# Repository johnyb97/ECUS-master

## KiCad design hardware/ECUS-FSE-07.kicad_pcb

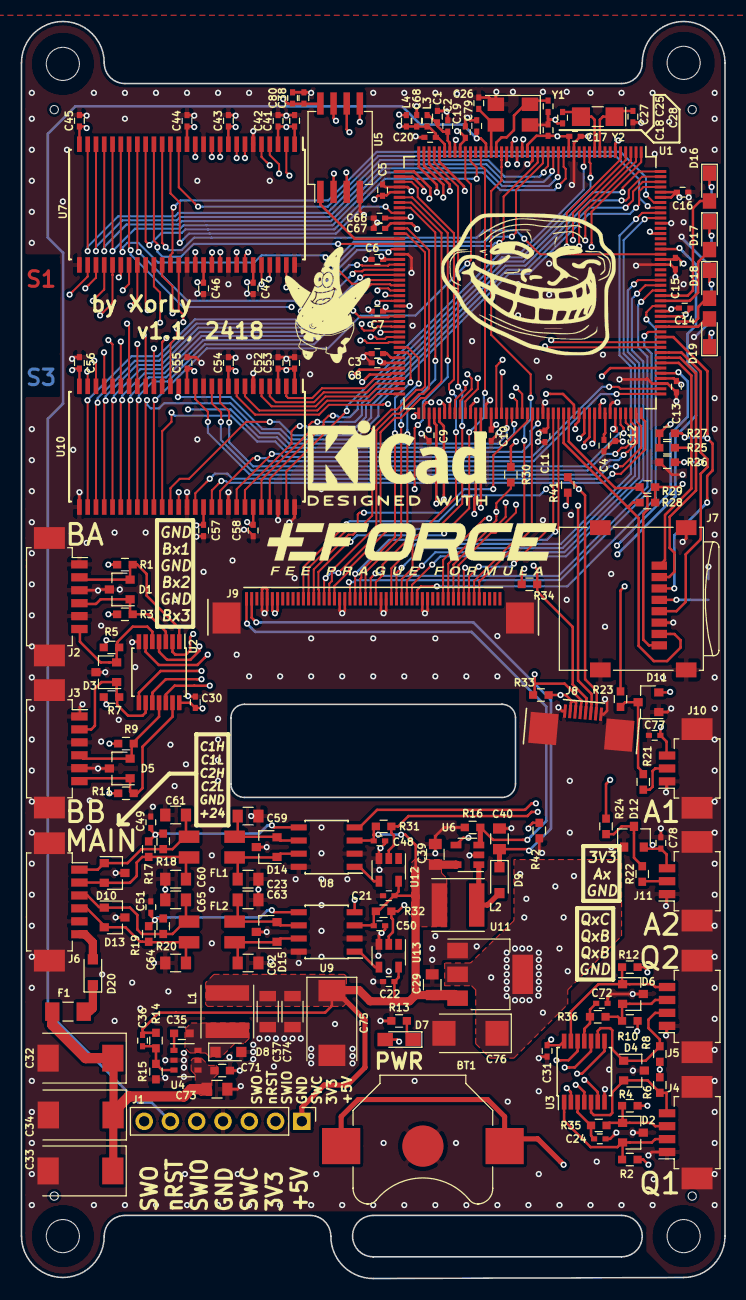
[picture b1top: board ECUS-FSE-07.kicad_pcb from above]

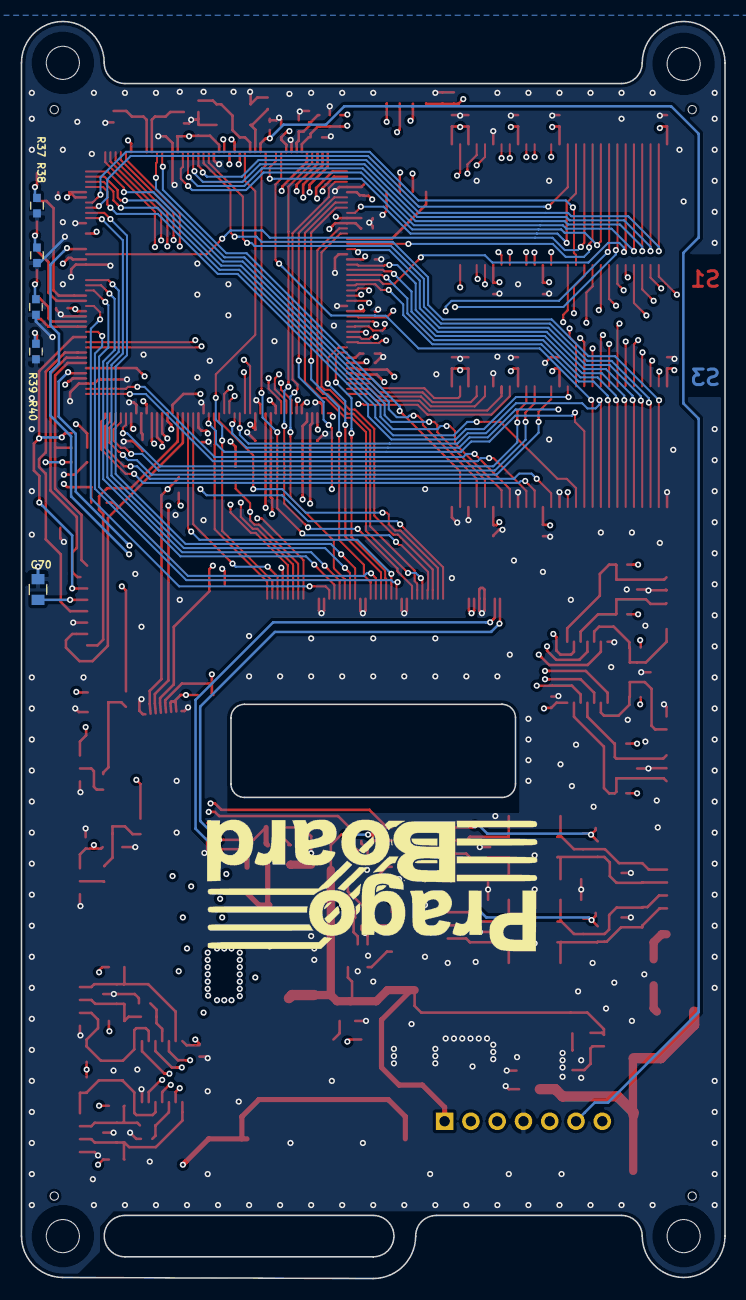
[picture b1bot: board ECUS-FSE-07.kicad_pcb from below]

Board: 6 copper layers, 68.0 x 121.5 mm, 189 parts (6 on the bottom side), 184 nets.

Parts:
BT1: BR-1225/VCN; Keystone_3000_1x12mm-CoinCell
C1, C3, C4, C68: 2.2u; C_0402_1005Metric_legacy
C2, C5, C6, C7, C8, C9, C10, C11, C12, C13, C14, C15, C16, C17, C18, C19, C20, C21, C22, C24, C30, C31, C36, C38, C48, C50, C72, C79: 100n; C_0402_1005Metric_legacy
C23, C59, C60, C61, C62, C63, C64, C65: Can; C_0805_2012Metric_legacy
C25, C26: 33p; C_0402_1005Metric_legacy
C27, C28: 15p; C_0402_1005Metric_legacy
C29, C39: 4.7u; C_0805_2012Metric_legacy
C32, C33, C34: 10u/35V; CP_EIA-7343-31_Kemet-D
C35: 15n/50V; C_0603_1608Metric_legacy
C37, C74: 10u; C_1206_3216Metric_legacy
C40: 220n/35V; C_0805_2012Metric_legacy
C41, C42, C43, C44, C45, C46, C47, C49, C51, C52, C53, C54, C55, C56, C57, C58: 10n; C_0402_1005Metric_legacy
C66, C67: Cain; C_0402_1005Metric_legacy
C70: 4u; C_0805_2012Metric_legacy
C71: 100n/50V; C_0603_1608Metric_legacy
C73: 1u/50V; C_0805_2012Metric_legacy
C75: 100u/10V; CP_EIA-7343-31_Kemet-D
C76: 22u/16V; CP_EIA-6032-28_Kemet-C_Pad2.24x2.40mm_HandSolder
C77, C78: C; C_0402_1005Metric_legacy
C80: 1u; C_0402_1005Metric_legacy
D1, D2, D3, D4, D5, D6: D_TVS_UNI_x2_CCA; SOT-23
D7: PWR; LED_0805_2012Metric_Pad0.97x1.50mm_HandSolder
D8, D9, D20: D_Schottky; D_SOD-323_HandSoldering
D10, D13, D14, D15: NUP2105L; SOT-23
D11, D12: BAV99; SOT-23
D16: LED1; LED_0805_2012Metric_Pad0.97x1.50mm_HandSolder
D17: LED2; LED_0805_2012Metric_Pad0.97x1.50mm_HandSolder
D18: LED3; LED_0805_2012Metric_Pad0.97x1.50mm_HandSolder
D19: LED4; LED_0805_2012Metric_Pad0.97x1.50mm_HandSolder
F1: Fuse; Fuse_1206_3216Metric_Pad1.39x1.80mm_HandSolder
FL1, FL2: EMI_Filter_LL; DLW43
J1: DBG; PinHeader_1x07_P2.54mm_Vertical
J2: BTN_A; Molex_PicoBlade_53261-0671_1x06-1MP_P1.25mm_Horizontal
J3: BTN_B; Molex_PicoBlade_53261-0671_1x06-1MP_P1.25mm_Horizontal
J4: QEI1; Molex_PicoBlade_53261-0471_1x04-1MP_P1.25mm_Horizontal
J5: QEI2; Molex_PicoBlade_53261-0471_1x04-1MP_P1.25mm_Horizontal
J6: main; Molex_PicoBlade_53261-0671_1x06-1MP_P1.25mm_Horizontal
J7: Micro_SD_Card_Det; microSD_HC_Wuerth_693072010801
J8: TC; FPC_08_0.5
J9: LCD; FPC_50_0.5
J10, J11: AIN; Molex_PicoBlade_53261-0371_1x03-1MP_P1.25mm_Horizontal
L1: 6.8u; L_Taiyo-Yuden_NR-50xx
L2: 33u; L_Taiyo-Yuden_NR-50xx
L3, L4: Ferrite_Bead_Small; C_0402_1005Metric_legacy
M1: DISPLAY_MODEL; LCD_ECUS
M2: eforce; eforce_28
M3: pragoboard
M4: bonus; troll_24
M5: kicad; kicad_18
M6: patrick; patrick_11
MK1, MK2, MK3, MK4: Mounting_Hole; MountingHole_3.2mm_M3_NoMask
MK5, MK6, MK7, MK8: LCD_Hole; Hole_0.8
R1, R2, R3, R4, R5, R6, R7, R8, R9, R10, R11, R12, R31, R32, R35, R36, R42: 1k; R_0603_larger_pads
R13, R37, R38, R39, R40: Rled; R_0603_larger_pads
R14: 3.9k; R_0603_larger_pads
R15: 680; R_0603_larger_pads
R16: 15; R_0603_larger_pads
R17, R18, R19, R20: 60; R_0603_larger_pads
R21, R22: Rain; R_0603_larger_pads
R23, R24: Rain2; R_0603_larger_pads
R25, R27, R28, R29: RuSD; R_0603_larger_pads
R26: RdSD; R_0603_larger_pads
R30, R41: 10k; R_0603_larger_pads
R33, R34: 4.7k; R_0603_larger_pads
U1: STM32F746IETx; LQFP-176_24x24mm_P0.5mm
U2, U3: 74LVC04; TSSOP-14_4.4x5mm_P0.65mm
U4: BD9G101G; TSOP-6_1.65x3.05mm_P0.95mm
U5: N25Q128A; SSO-8_6.8x5.9mm_P1.27mm_Clearance7mm
U6: CAT4237; SOT-23-5
U7, U10: IS42S16400; TSOP_II_54_10.16x22.22_Pitch0.8mm
U8, U9: TJA1049T; SOIC-8_3.9x4.9mm_P1.27mm
U11: AP1117-33; SOT-223-3_TabPin2
U12, U13: 74LVC1G17; SOT-23-5
Y1: 8MHz 18pF; Crystal_SMD_5032-4Pin_5.0x3.2mm
Y2: 32.768 kHz 9pF; Crystal_SMD_MicroCrystal_CC7V-T1A-2Pin_3.2x1.5mm_HandSolder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

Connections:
+3V3: C5.1, C6.1, C7.1, C8.1, C9.1, C10.1, C11.1, C12.1, C13.1, C14.1, C15.1, C16.1, C17.1, C18.1, C19.1, C30.1, C31.1, C38.1, C41.1, C42.1, C43.1, C44.1, C45.1, C46.1, C47.1, C52.1, C53.1, C54.1, C55.1, C56.1, C57.1, C58.1, C70.1, C76.1, C77.2, C78.2, C80.1, D7.2, D11.2, D12.2, J1.2, J7.4, J8.2, J8.3, J9.6, J9.7, J10.3, J11.3, L4.2, R1.1, R2.1, R3.1, R4.1, R5.1, R6.1, R7.1, R8.1, R9.1, R10.1, R11.1, R12.1, R25.1, R27.1, R28.1, R29.1, R30.1, R33.1, R34.1, R41.1, U1.15, U1.23, U1.36, U1.49, U1.62, U1.72, U1.82, U1.91, U1.103, U1.114, U1.127, U1.136, U1.149, U1.159, U1.171, U1.172, U2.14, U3.14, U5.8, U7.1, U7.3, U7.9, U7.14, U7.27, U7.43, U7.49, U10.1, U10.3, U10.9, U10.14, U10.27, U10.43, U10.49, U11.2
+5V: C21.1, C22.1, C29.1, C36.1, C37.1, C39.1, C48.1, C50.1, C74.1, C75.1, J1.1, L1.2, L2.1, R14.1, R31.1, R32.1, U6.5, U8.3, U9.3, U11.3, U12.5, U13.5
+24V: C32.1, C33.1, C34.1, C71.1, C73.1, F1.2, U4.4, U4.5
/AIN_1: C66.2, R23.2, U1.54
/AIN_2: C67.2, R24.2, U1.55
/BTN_A1: U1.83, U2.2
/BTN_A2: U1.84, U2.4
/BTN_A3: U1.94, U2.6
/BTN_B1: U1.95, U2.8
/BTN_B2: U1.99, U2.10
/BTN_B3: U1.119, U2.12
/CAN1_H: C60.1, D10.2, FL1.2, J6.2, R17.1
/CAN1_L: C61.1, D10.1, FL1.4, J6.1, R18.2
/CAN1_RX: U1.122, U8.4
/CAN1_TX: R31.2, U1.123, U12.2
/CAN2_H: C64.1, D13.2, FL2.2, J6.4, R19.1
/CAN2_L: C65.1, D13.1, FL2.4, J6.3, R20.2
/CAN2_RX: U1.92, U9.4
/CAN2_TX: R32.2, U1.93, U13.2
/FLASH_CLK: U1.58, U5.1
/FLASH_IO0: U1.26, U5.5
/FLASH_IO1: U1.27, U5.2
/FLASH_IO2: U1.25, U5.3
/FLASH_IO3: U1.24, U5.7
/FLASH_nCS: U1.164, U5.6
/I2C4_SCL: J8.4, R33.2, U1.100
/I2C4_SDA: J8.5, R34.2, U1.101
/LCD/LED_A: C40.1, D9.1, J9.2
/LCD/LED_K: J9.1, R16.1, U6.3
/LCD_B2: J9.34, U1.150
/LCD_B3: J9.33, U1.154
/LCD_B4: J9.32, U1.155
/LCD_B5: J9.31, U1.47
/LCD_B6: J9.30, U1.167
/LCD_B7: J9.29, U1.168
/LCD_BLCTL: R42.1, U1.138, U6.4
/LCD_CLK: J9.46, U1.111
/LCD_CTL_MISO: J9.42, U1.4
/LCD_CTL_MOSI: J9.41, U1.5
/LCD_CTL_RST: J9.12, U1.2
/LCD_CTL_SCK: J9.39, U1.1
/LCD_CTL_~CS: J9.40, R30.2, U1.3
/LCD_DE: J9.45, U1.28
/LCD_G2: J9.26, U1.52
/LCD_G3: J9.25, U1.153
/LCD_G4: J9.24, U1.79
/LCD_G5: J9.23, U1.80
/LCD_G6: J9.22, U1.116
/LCD_G7: J9.21, U1.145
/LCD_HSYNC: J9.44, U1.115
/LCD_R2: J9.18, U1.41
/LCD_R3: J9.17, U1.56
/LCD_R4: J9.16, U1.51
/LCD_R5: J9.15, U1.32
/LCD_R6: J9.14, U1.57
/LCD_R7: J9.13, U1.110
/LCD_VSYNC: J9.43, U1.50
/LED1: D16.2, U1.152
/LED2: D17.2, U1.151
/LED3: D18.2, U1.147
/LED4: D19.2, U1.146
/QE1_A: U1.40, U3.2
/QE1_B: U1.42, U3.4
/QE1_C: U1.43, U3.6
/QE2_A: U1.44, U3.8
/QE2_B: U1.45, U3.10
/QE2_C: U1.46, U3.12
/RAM_A0: U1.16, U7.23, U10.23
/RAM_A1: U1.17, U7.24, U10.24
/RAM_A2: U1.18, U7.25, U10.25
/RAM_A3: U1.19, U7.26, U10.26
/RAM_A4: U1.20, U7.29, U10.29
/RAM_A5: U1.21, U7.30, U10.30
/RAM_A6: U1.60, U7.31, U10.31
/RAM_A7: U1.63, U7.32, U10.32
/RAM_A8: U1.64, U7.33, U10.33
/RAM_A9: U1.65, U7.34, U10.34
/RAM_A10: U1.66, U7.22, U10.22
/RAM_A11: U1.67, U7.35, U10.35
/RAM_A12: U1.106, U7.36, U10.36
/RAM_A13: U1.107, U7.40, U10.40
/RAM_BA0: U1.108, U7.20, U10.20
/RAM_BA1: U1.109, U7.21, U10.21
/RAM_CAS: U1.160, U7.17, U10.17
/RAM_CKE: U1.35, U7.37, U10.37
/RAM_CLK: U1.112, U7.38, U10.38
/RAM_CS: U1.34, U7.19, U10.19
/RAM_DE0: U1.169, U7.15
/RAM_DE1: U1.170, U7.39
/RAM_DE2: U1.173, U10.15
/RAM_DE3: U1.174, U10.39
/RAM_DH0: U1.85, U10.2
/RAM_DH1: U1.86, U10.4
/RAM_DH2: U1.87, U10.5
/RAM_DH3: U1.88, U10.7
/RAM_DH4: U1.89, U10.8
/RAM_DH5: U1.128, U10.10
/RAM_DH6: U1.129, U10.11
/RAM_DH7: U1.130, U10.13
/RAM_DH8: U1.131, U10.42
/RAM_DH9: U1.132, U10.44
/RAM_DH10: U1.133, U10.45
/RAM_DH11: U1.134, U10.47
/RAM_DH12: U1.175, U10.48
/RAM_DH13: U1.176, U10.50
/RAM_DH14: U1.11, U10.51
/RAM_DH15: U1.12, U10.53
/RAM_DL0: U1.104, U7.2
/RAM_DL1: U1.105, U7.4
/RAM_DL2: U1.142, U7.5
/RAM_DL3: U1.143, U7.7
/RAM_DL4: U1.68, U7.8
/RAM_DL5: U1.69, U7.10
/RAM_DL6: U1.70, U7.11
/RAM_DL7: U1.73, U7.13
/RAM_DL8: U1.74, U7.42
/RAM_DL9: U1.75, U7.44
/RAM_DL10: U1.76, U7.45
/RAM_DL11: U1.77, U7.47
/RAM_DL12: U1.78, U7.48
/RAM_DL13: U1.96, U7.50
/RAM_DL14: U1.97, U7.51
/RAM_DL15: U1.98, U7.53
/RAM_RAS: U1.59, U7.18, U10.18
/RAM_WE: U1.53, U7.16, U10.16
/SD_CLK: J7.5, U1.141
/SD_CMD: J7.3, R27.2, U1.144
/SD_DAT0: J7.7, R28.2, U1.117
/SD_DAT1: J7.8, R29.2, U1.118
/SD_DAT2: J7.1, R25.2, U1.139
/SD_DAT3: J7.2, R26.1, U1.140
/SWCLK: J1.3, U1.137
/SWDIO: J1.5, U1.124
/SWO: J1.7, U1.161
/TC_INT: J8.6, U1.120
/TC_RST: J8.7, R41.2, U1.121
/VDDA: C20.1, C68.1, L3.1, L4.1, U1.39
/XTAL32_IN: C27.1, U1.9, Y2.1
/XTAL32_OUT: C28.1, U1.10, Y2.2
/XTAL_IN: C25.1, U1.29, Y1.1
/XTAL_OUT: C26.1, U1.30, Y1.3
/nRST: C79.1, J1.6, U1.31
GND: BT1.2, C1.2, C2.2, C3.2, C4.2, C5.2, C6.2, C7.2, C8.2, C9.2, C10.2, C11.2, C12.2, C13.2, C14.2, C15.2, C16.2, C17.2, C18.2, C19.2, C20.2, C21.2, C22.2, C23.2, C24.2, C25.2, C26.2, C27.2, C28.2, C29.2, C30.2, C31.2, C32.2, C33.2, C34.2, C37.2, C38.2, C39.2, C40.2, C41.2, C42.2, C43.2, C44.2, C45.2, C46.2, C47.2, C48.2, C49.2, C50.2, C51.2, C52.2, C53.2, C54.2, C55.2, C56.2, C57.2, C58.2, C59.2, C60.2, C61.2, C62.2, C63.2, C64.2, C65.2, C66.1, C67.1, C68.2, C70.2, C71.2, C72.2, C73.2, C74.2, C75.2, C76.2, C77.1, C78.1, C79.2, C80.2, D1.3, D2.3, D3.3, D4.3, D5.3, D6.3, D8.2, D10.3, D11.1, D12.1, D13.3, D14.3, D15.3, J1.4, J2.1, J2.3, J2.5, J2.MP, J3.1, J3.3, J3.5, J3.MP, J4.1, J4.MP, J5.1, J5.MP, J6.5, J6.MP, J7.6, J7.9, J8.1, J8.8, J8.MP, J9.4, J9.5, J9.19, J9.20, J9.27, J9.28, J9.35, J9.36, J9.MP, J10.1, J10.MP, J11.1, J11.MP, R13.2, R15.2, R16.2, R26.2, R37.2, R38.2, R39.2, R40.2, R42.2, U1.14, U1.22, U1.37, U1.48, U1.61, U1.71, U1.90, U1.102, U1.113, U1.126, U1.135, U1.148, U1.158, U1.166, U2.7, U3.7, U4.2, U5.4, U6.2, U7.6, U7.12, U7.28, U7.41, U7.46, U7.52, U7.54, U8.2, U8.8, U9.2, U9.8, U10.6, U10.12, U10.28, U10.41, U10.46, U10.52, U10.54, U11.1, U12.3, U13.3, Y1.2, Y1.4
unnamed: BT1.1, U1.6
unnamed: C1.1, C2.1, L3.2, U1.38
unnamed: C3.1, U1.81
unnamed: C4.1, U1.125
unnamed: C23.1, D14.1, FL1.1, U8.7
unnamed: C24.1, R35.1, U3.3
unnamed: C35.1, D8.1, L1.1, U4.6
unnamed: C35.2, U4.1
unnamed: C36.2, R14.2, R15.1, U4.3
unnamed: C49.1, R17.2, R18.1, U8.5
unnamed: C51.1, R19.2, R20.1, U9.5
unnamed: C59.1, D14.2, FL1.3, U8.6
unnamed: C62.1, D15.1, FL2.1, U9.7
unnamed: C63.1, D15.2, FL2.3, U9.6
unnamed: C72.1, R36.1, U3.11
unnamed: D1.1, J2.4, R3.2, U2.3
unnamed: D1.2, J2.2, R1.2, U2.1
unnamed: D2.1, J4.3, R4.2, R35.2
unnamed: D2.2, J4.2, R2.2, U3.1
unnamed: D3.1, J3.2, R7.2, U2.9
unnamed: D3.2, J2.6, R5.2, U2.5
unnamed: D4.1, J5.2, R8.2, U3.9
unnamed: D4.2, J4.4, R6.2, U3.5
unnamed: D5.1, J3.6, R11.2, U2.13
unnamed: D5.2, J3.4, R9.2, U2.11
unnamed: D6.1, J5.4, R12.2, U3.13
unnamed: D6.2, J5.3, R10.2, R36.2
unnamed: D7.1, R13.1
unnamed: D9.2, L2.2, U6.1
unnamed: D11.3, R21.2, R23.1
unnamed: D12.3, R22.2, R24.1
unnamed: D16.1, R37.1
unnamed: D17.1, R38.1
unnamed: D18.1, R39.1
unnamed: D19.1, R40.1
unnamed: D20.1, F1.1
unnamed: D20.2, J6.6
unnamed: J10.2, R21.1
unnamed: J11.2, R22.1
unnamed: U8.1, U12.4
unnamed: U9.1, U13.4

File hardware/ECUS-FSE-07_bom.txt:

Reference, Quantity, Value, Footprint, Datasheet, mpn

mouser
BT1 ,1,"BR-1225/VCN","efoce_misc:Keystone_3000_1x12mm-CoinCell","","3000"
D10 D13 D14 D15 ,4,"NUP2105L","Package_TO_SOT_SMD:SOT-23","","SZNUP2105LT3G"
D11 D12 ,2,"BAV99","Package_TO_SOT_SMD:SOT-23","","BAV99"
D1 D2 D3 D4 D5 D6 ,6,"D_TVS_UNI_x2_CCA","Package_TO_SOT_SMD:SOT-23","","PESD3V3S2UT"
D8 D9 ,2,"D_Schottky","Diode_SMD:D_SOD-323_HandSoldering","","CMDSH05-45 TR"
F1 ,1,"Fuse","Fuse:Fuse_1206_3216Metric_Pad1.24x1.80mm_HandSolder","","C1Q 250"
FL1 FL2 ,2,"EMI_Filter_LL","eforce_misc:DLW43","","DLW43SH510XK2L"
J10 J11 ,2,"AIN","Connectors_Molex:Molex_PicoBlade_53261-0371_03x1.25mm_Angled","","53261-0371"
J2 ,1,"BTN_A","Connectors_Molex:Molex_PicoBlade_53261-0671_06x1.25mm_Angled","","53261-0671"
J3 ,1,"BTN_B","Connectors_Molex:Molex_PicoBlade_53261-0671_06x1.25mm_Angled","","53261-0671"
J4 ,1,"QE1","Connectors_Molex:Molex_PicoBlade_53261-0471_04x1.25mm_Angled","","53261-0471"
J5 ,1,"QE2","Connectors_Molex:Molex_PicoBlade_53261-0471_04x1.25mm_Angled","","53261-0471"
J6 ,1,"main","Connectors_Molex:Molex_PicoBlade_53261-0771_07x1.25mm_Angled","","53261-0771"
R16 ,1,"15","Capacitor_SMD_legacy:C_0603_1608Metric","","CRCW060315R0FKEA"
U2 U3 ,2,"74LVC04","Package_SO:TSSOP-14_4.4x5mm_P0.65mm","","SN74LVC04APWR"
U5 ,1,"N25Q128A","Package_SO:SOIC-8_3.9x4.9mm_P1.27mm","","six"
U10 U7 ,2,"IS42S16400","eforce_misc:TSOP_II_54_10.16x22.22_Pitch0.8mm","","IS42S16400J-7TL"
Y1 ,1,"8MHz 18pF","Crystal:Crystal_SMD_5032-4Pin_5.0x3.2mm","","LFXTAL055663Bulk"
Y2 ,1,"32.768 kHz 9pF","Crystal:Crystal_SMD_MicroCrystal_CC7V-T1A-2Pin_3.2x1.5mm_HandSoldering","","LFXTAL009706Reel"
C32 C33 C34 ,3,"10u","Capacitor_Tantalum_SMD:CP_EIA-7343-31_Kemet-D","","293D106X9035D2WE3"

L3 L4 ,2,"Ferrite_Bead_Small","Capacitor_SMD_legacy:C_0402_1005Metric","","7427927121"
C25 C26 ,2,"33p","Capacitor_SMD_legacy:C_0402_1005Metric","","885012005028"
C27 C28 ,2,"15p","Capacitor_SMD_legacy:C_0402_1005Metric","","885012005026"
C1 C3 C4 C68 ,4,"2.2u","Capacitor_SMD_legacy:C_0402_1005Metric","","885012105013"
C41 C42 C43 C44 C45 C46 C47 C49 C51 C52 C53 C54 C55 C56 C57 C58 ,16,"10n","Capacitor_SMD_legacy:C_0402_1005Metric","","885012205031"
C10 C11 C12 C13 C14 C15 C16 C17 C18 C19 C2 C20 C21 C22 C24 C30 C31 C36 C38 C48 C5 C50 C6 C7 C8 C9 ,26,"100n","Capacitor_SMD_legacy:C_0402_1005Metric","","885012205037"
L1 ,1,"6.8u","Inductors:Inductor_Wurth_HCI-5040","","74405042068"
L2 ,1,"33u","Inductor_SMD:L_Taiyo-Yuden_NR-50xx_HandSolder","","74404043330A"
C37 ,1,"10u","Capacitor_SMD_legacy:C_0805_2012Metric","","885012107010"
C29 C39 ,2,"4.7u","Capacitor_SMD_legacy:C_0805_2012Metric","","885012107006"
C35 ,1,"15n/50V","Capacitor_SMD_legacy:C_0603_1608Metric","","885012206090"
J7 ,1,"Micro_SD_Card","Connector_Card:microSD_HC_Wuerth_693072010801","","693072010801"


MK1 MK2 MK3 MK4 ,4,"Mounting_Hole_PAD","Mounting_Holes:MountingHole_2.7mm_Pad","","dnp"
M1 ,1,"DISPLAY_MODEL","eforce_misc:LCD_ECUS","","dnp"
MK5 MK6 MK7 MK8 ,4,"LCD_Hole","eforce_misc:Hole_0.6","","dnp"


C40 ,1,"220n/35V","Capacitor_SMD_legacy:C_0805_2012Metric","","ef"
C66 C67 ,2,"Cain","Capacitor_SMD_legacy:C_0402_1005Metric","","ef"
D7 ,1,"PWR","LED_SMD:LED_0805_2012Metric_Pad0.97x1.50mm_HandSolder","","ef"
J1 ,1,"DEBUG","eforce_misc:Pin_Header_Edge_2x03_P2.54mm_SMD","","ef"
J8 ,1,"TC","eforce_misc:FPC_08_0.5","","ef"
J9 ,1,"LCD","eforce_misc:FPC_50_0.5_INV","","ef"
R13 ,1,"Rled","Capacitor_SMD_legacy:C_0603_1608Metric","","ef"
R14 ,1,"3.9k","Capacitor_SMD_legacy:C_0603_1608Metric","","ef"
R15 ,1,"680","Capacitor_SMD_legacy:C_0603_1608Metric","","ef"
R17 R18 R19 R20 ,4,"60","Capacitor_SMD_legacy:C_0603_1608Metric","","ef"
R21 R22 ,2,"Rain","Capacitor_SMD_legacy:C_0603_1608Metric","","ef"
R23 R24 ,2,"Rain2","Capacitor_SMD_legacy:C_0603_1608Metric","","ef"
R26 ,1,"RdSD","Capacitor_SMD_legacy:C_0603_1608Metric","","ef"
R25 R27 R28 R29 ,4,"RuSD","Capacitor_SMD_legacy:C_0603_1608Metric","","ef"
R30 ,1,"10k","Capacitor_SMD_legacy:C_0603_1608Metric","","ef"
R1 R10 R11 R12 R2 R3 R4 R5 R6 R7 R8 R9 ,12,"1k","Capacitor_SMD_legacy:C_0603_1608Metric","","ef"
U4 ,1,"BD9G101G","Package_SO:TSOP-6_1.65x3.05mm_P0.95mm","","ef"
U6 ,1,"CAT4237","Package_TO_SOT_SMD:SOT-23-5","","ef"
U8 U9 ,2,"TJA1049T","Package_SO:SOIC-8_3.9x4.9mm_P1.27mm","","ef"
C23 C59 C60 C61 C62 C63 C64 C65 ,8,"Can","Capacitor_SMD_legacy:C_0805_2012Metric","","dnp/ef"

STM
U1 ,1,"STM32F746IETx","Package_QFP:LQFP-176_24x24mm_P0.5mm","http://www.st.com/st-web-ui/static/active/en/resource/techni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","STM"

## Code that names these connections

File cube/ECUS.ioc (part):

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Mcu.Name=STM32F746IGTx
Mcu.Package=LQFP176
Mcu.UserName=STM32F746IGTx
PA0/WKUP.GPIOParameters=GPIO_Label
PA0/WKUP.GPIO_Label=QEI1_A
PA0/WKUP.Signal=GPXTI0
PA1.Mode=RGB666
PA1.Signal=LTDC_R2
PA10.GPIOParameters=GPIO_Label
PA10.GPIO_Label=TC_RST
PA10.Signal=GPIO_Output
PA11.Mode=Master
PA11.Signal=CAN1_RX
PA12.Mode=Master
PA12.Signal=CAN1_TX
PA13.Mode=Trace_Asynchronous_SW
PA13.Signal=SYS_JTMS-SWDIO
PA14.Mode=Trace_Asynchronous_SW
PA14.Signal=SYS_JTCK-SWCLK
PA15.GPIOParameters=GPIO_Label
PA15.GPIO_Label=BLCTL
PA15.Signal=S_TIM2_CH1_ETR
PA2.GPIOParameters=GPIO_Label
PA2.GPIO_Label=QEI1_B_EXTI2
PA2.Signal=GPIO_Input
PA3.Mode=RGB666
PA3.Signal=LTDC_B5
PA4.Mode=RGB666
PA4.Signal=LTDC_VSYNC
PA5.Mode=RGB666
PA5.Signal=LTDC_R4
PA6.Mode=RGB666
PA6.Signal=LTDC_G2
PA7.Signal=FMC_SDNWE
PA8.GPIOParameters=GPIO_Label
PA8.GPIO_Label=BTN_B3
PA8.Signal=GPIO_Input
PA9.GPIOParameters=GPIO_Label
PA9.GPIO_Label=TC_INT_EXTI9
PA9.Signal=GPXTI9
PB0.Mode=RGB666
PB0.Signal=LTDC_R3
PB1.Mode=RGB666
PB1.Signal=LTDC_R6
PB10.Mode=RGB666
PB10.Signal=LTDC_G4
PB11.Mode=RGB666
PB11.Signal=LTDC_G5
PB12.Mode=Slave
PB12.Signal=CAN2_RX
PB13.Mode=Slave
PB13.Signal=CAN2_TX
PB14.GPIOParameters=GPIO_Label
PB14.GPIO_Label=BTN_A3
PB14.Signal=GPIO_Input
PB15.GPIOParameters=GPIO_Label
PB15.GPIO_Label=BTN_B1
PB15.Signal=GPIO_Input
PB2.Mode=Single Bank 1
PB2.Signal=QUADSPI_CLK
PB3.Mode=Trace_Asynchronous_SW
PB3.Signal=SYS_JTDO-SWO
PB6.Mode=Single Bank 1
PB6.Signal=QUADSPI_BK1_NCS
PB8.Mode=RGB666
PB8.Signal=LTDC_B6
PB9.Mode=RGB666
PB9.Signal=LTDC_B7
PC0.Mode=RGB666
PC0.Signal=LTDC_R5
PC10.Mode=SD_4_bits_Wide_bus
PC10.Signal=SDMMC1_D2
PC11.Mode=SD_4_bits_Wide_bus
PC11.Signal=SDMMC1_D3
PC12.Mode=SD_4_bits_Wide_bus
PC12.Signal=SDMMC1_CK
PC14/OSC32_IN.Mode=LSE-External-Oscillator
PC14/OSC32_IN.Signal=RCC_OSC32_IN
PC15/OSC32_OUT.Mode=LSE-External-Oscillator
PC15/OSC32_OUT.Signal=RCC_OSC32_OUT
PC2.Mode=SdramChipSelect1_1
PC2.Signal=FMC_SDNE0
PC3.Mode=SdramChipSelect1_1
PC3.Signal=FMC_SDCKE0
PC4.GPIOParameters=GPIO_Label
PC4.GPIO_Label=AIN1
PC4.Signal=ADCx_IN14
PC5.GPIOParameters=GPIO_Label
PC5.GPIO_Label=AIN2
PC5.Signal=ADCx_IN15
PC6.Mode=RGB666
PC6.Signal=LTDC_HSYNC
PC7.Mode=RGB666
PC7.Signal=LTDC_G6
PC8.Mode=SD_4_bits_Wide_bus
PC8.Signal=SDMMC1_D0
PC9.Mode=SD_4_bits_Wide_bus
PC9.Signal=SDMMC1_D1
PD0.Signal=FMC_D2_DA2
PD1.Signal=FMC_D3_DA3
PD10.Signal=FMC_D15_DA15
PD11.GPIOParameters=GPIO_Label
PD11.GPIO_Label=BTN_B2
PD11.Signal=GPIO_Input
PD12.Mode=I2C
PD12.Signal=I2C4_SCL
PD13.Mode=I2C
PD13.Signal=I2C4_SDA
PD14.Signal=FMC_D0_DA0
PD15.Signal=FMC_D1_DA1
PD2.Mode=SD_4_bits_Wide_bus
PD2.Signal=SDMMC1_CMD
PD3.Mode=RGB666
PD3.Signal=LTDC_G7
PD4.GPIOParameters=GPIO_Label
PD4.GPIO_Label=LED4
PD4.Signal=GPIO_Output
PD5.GPIOParameters=GPIO_Label
PD5.GPIO_Label=LED3
PD5.Signal=GPIO_Output
PD6.Mode=RGB666
PD6.Signal=LTDC_B2
PD7.GPIOParameters=GPIO_Label
PD7.GPIO_Label=LED2
PD7.Signal=GPIO_Output
PD8.Signal=FMC_D13_DA13
PD9.Signal=FMC_D14_DA14
PE0.Signal=FMC_NBL0
PE1.Signal=FMC_NBL1
PE10.Signal=FMC_D7_DA7
PE11.Signal=FMC_D8_DA8
PE12.Signal=FMC_D9_DA9
PE13.Signal=FMC_D10_DA10
PE14.Signal=FMC_D11_DA11
PE15.Signal=FMC_D12_DA12
PE2.Mode=Full_Duplex_Master
PE2.Signal=SPI4_SCK
PE3.GPIOParameters=GPIO_Label
PE3.GPIO_Label=LCD_RST
PE3.Signal=GPIO_Output
PE4.GPIOParameters=GPIO_Label
PE4.GPIO_Label=LCD_nCS
PE4.Signal=GPIO_Output
PE5.Mode=Full_Duplex_Master
PE5.Signal=SPI4_MISO
PE6.Mode=Full_Duplex_Master
PE6.Signal=SPI4_MOSI
PE7.Signal=FMC_D4_DA4
PE8.Signal=FMC_D5_DA5
PE9.Signal=FMC_D6_DA6
PF0.Signal=FMC_A0
PF1.Signal=FMC_A1
PF10.Mode=RGB666
PF10.Signal=LTDC_DE
PF11.Signal=FMC_SDNRAS
PF12.Signal=FMC_A6
PF13.Signal=FMC_A7
PF14.Signal=FMC_A8
PF15.Signal=FMC_A9
PF2.Signal=FMC_A2
PF3.Signal=FMC_A3
PF4.Signal=FMC_A4
PF5.Signal=FMC_A5
PF6.Mode=Single Bank 1
PF6.Signal=QUADSPI_BK1_IO3
PF7.Mode=Single Bank 1
PF7.Signal=QUADSPI_BK1_IO2
PF8.Mode=Single Bank 1
PF8.Signal=QUADSPI_BK1_IO0
PF9.Mode=Single Bank 1
PF9.Signal=QUADSPI_BK1_IO1
PG0.Signal=FMC_A10
PG1.Signal=FMC_A11
PG10.Mode=RGB666
PG10.Signal=LTDC_G3
PG11.Mode=RGB666
PG11.Signal=LTDC_B3
PG12.Mode=RGB666
PG12.Signal=LTDC_B4
PG15.Signal=FMC_SDNCAS
PG2.Signal=FMC_A12
PG3.Signal=FMC_A13
PG4.Signal=FMC_A14_BA0
PG5.Signal=FMC_A15_BA1
PG6.Mode=RGB666
PG6.Signal=LTDC_R7
PG7.Mode=RGB666
PG7.Signal=LTDC_CLK
PG8.Signal=FMC_SDCLK
PG9.GPIOParameters=GPIO_Label
PG9.GPIO_Label=LED1
PG9.Signal=GPIO_Output
PH0/OSC_IN.Mode=HSE-External-Oscillator
PH0/OSC_IN.Signal=RCC_OSC_IN
PH1/OSC_OUT.Mode=HSE-External-Oscillator
PH1/OSC_OUT.Signal=RCC_OSC_OUT
PH10.Signal=FMC_D18
PH11.Signal=FMC_D19
PH12.Signal=FMC_D20
PH13.Signal=FMC_D21
PH14.Signal=FMC_D22
PH15.Signal=FMC_D23
PH2.GPIOParameters=GPIO_Label
PH2.GPIO_Label=QEI1_C
PH2.Signal=GPIO_Input
PH3.GPIOParameters=GPIO_Label
PH3.GPIO_Label=QEI2_A
PH3.Signal=GPXTI3
PH4.GPIOParameters=GPIO_Label
PH4.GPIO_Label=QEI2_B_EXTI4
PH4.Signal=GPIO_Input
PH5.GPIOParameters=GPIO_Label
PH5.GPIO_Label=QEI2_C
PH5.Signal=GPIO_Input
PH6.GPIOParameters=GPIO_Label
PH6.GPIO_Label=BTN_A1
PH6.Signal=GPIO_Input
PH7.GPIOParameters=GPIO_Label
PH7.GPIO_Label=BTN_A2
PH7.Signal=GPIO_Input
PH8.Signal=FMC_D16
PH9.Signal=FMC_D17
PI0.Signal=FMC_D24
PI1.Signal=FMC_D25
PI10.Signal=FMC_D31
PI2.Signal=FMC_D26
PI3.Signal=FMC_D27
PI4.Signal=FMC_NBL2
PI5.Signal=FMC_NBL3
PI6.Signal=FMC_D28
PI7.Signal=FMC_D29
PI9.Signal=FMC_D30
RCC.HSE_VALUE=8000000
RCC.SYSCLKFreq_VALUE=200000000
RCC.SYSCLKSource=RCC_SYSCLKSOURCE_PLLCLK
